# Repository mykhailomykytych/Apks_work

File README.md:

# Лабораторна робота №1 — AI-агент для автоматизації розробки та CI/CD

| | |
|---|---|
| **Студент** | Микитич Михайло Васильович |
| **Група** | КІ-407 |
| **Варіант** | 6 (номер у списку 12): TypeScript · npm scripts · Vitest |

## Опис
Репозиторій містить AI-агента **build-engineer** для GitHub Copilot (VS Code),
який генерує, складає, тестує та налаштовує CI для кросплатформного
TypeScript-проєкту `Hello World`.

- Гілка `develop` — лише агент (manifest, skills, commands) та документація.
- Гілка `feature/lab1-hello-world` — повний результат роботи агента: вихідний код,
  тести, система складання, CI-скрипти та GitHub Actions.

## Структура агента
| Елемент | Файл |
|---|---|
| Agent manifest | `.github/agents/build-engineer.agent.md` |
| Skill `project-scaffold` | `.github/skills/project-scaffold/SKILL.md` |
| Skill `build-and-test` | `.github/skills/build-and-test/SKILL.md` |
| Skill `github-actions` | `.github/skills/github-actions/SKILL.md` |
| Commands | `.github/prompts/{git-init,create-project,create-build,create-actions,check}.prompt.md` |
| Orchestrator | `.github/prompts/init.prompt.md` |

## Запуск агента (коротко)
1. Відкрити репозиторій у VS Code з увімкненим GitHub Copilot.
2. Відкрити Copilot Chat, обрати агента **build-engineer**.
3. Ввести `/init` і дочекатися звіту `init COMPLETED`.

Детально — у [docs/usage.md](docs/usage.md). Архітектура — у
[docs/architecture.md](docs/architecture.md). Журнал роботи з AI —
[docs/ai-log.md](docs/ai-log.md).

## Запуск зібраного проєкту
```bash
npm ci
npm run build
npm start              # Hello, World!
npm test               # Vitest, включно з BasicAddition
npm run package        # створює виконуваний файл bin/hello (bin\hello.exe)
./bin/hello            # Hello, World!
```
Повний CI-сценарій локально: `./scripts/ci.sh` (Linux/macOS) або `scripts\ci.bat` (Windows).

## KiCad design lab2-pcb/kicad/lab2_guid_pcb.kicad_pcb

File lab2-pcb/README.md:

# Лабораторна робота №2 — друкована плата за GUID (KiCad)

| | |
|---|---|
| **Студент** | Микитич Михайло Васильович |
| **Група** | КІ-407 |
| **САПР** | KiCad 7 (файли відкриваються в KiCad 7/8/9) |

## 1. GUID
GUID отримано хешуванням повного імені (UUID v5, SHA-1, простір імен DNS):

```python
import uuid
uuid.uuid5(uuid.NAMESPACE_DNS, "Микитич Михайло Васильович")
# 8c0f2d7a-9934-50b1-a59d-aba02fab321b
```

## 2. Розміри елементів
| Елемент | Група GUID | Символів | Розмір, мм | Пінів |
|---|---|---|---|---|
| U1 | `8c0f2d7a` | 8 | 8 × 8 | 8 |
| U2 | `9934` | 4 | 4 × 4 | 4 |
| U3 | `50b1` | 4 | 4 × 4 | 4 |
| U4 | `a59d` | 4 | 4 × 4 | 4 |
| U5 | `aba02fab321b` | 12 | 12 × 12 | 12 |

Нумерація пінів: проти годинникової стрілки від лівого верхнього (як у QFP);
пін *k* відповідає *k*-му символу групи.

## 3. Таблиця з'єднань
Однакові символи — це рівнозначні піни, тому їх з'єднано.

| Символ | Ланцюг | Піни |
|---|---|---|
| `0` | N_0 | U1.3, U3.2, U5.4 |
| `1` | N_1 | U3.4, U5.11 |
| `2` | N_2 | U1.5, U5.5, U5.10 |
| `3` | N_3 | U2.3, U5.9 |
| `5` | N_5 | U3.1, U4.2 |
| `9` | N_9 | U2.1, U2.2, U4.3 |
| `a` | N_A | U1.8, U4.1, U5.1, U5.3, U5.7 |
| `b` | N_B | U3.3, U5.2, U5.8, U5.12 |
| `d` | N_D | U1.6, U4.4 |
| `f` | N_F | U1.4, U5.6 |

Вільні піни (символ трапляється один раз) виведено на роз'єм **J1** на
лівій (меншій) стороні плати:

| Символ | Пін | J1 |
|---|---|---|
| `4` | U2.4 | J1.1 |
| `7` | U1.7 | J1.2 |
| `8` | U1.1 | J1.3 |
| `c` | U1.2 | J1.4 |

## 4. Плата
- Контур: **85.6 × 53.98 мм** (кредитна картка ID-1), радіус кутів 3.18 мм.
- 2 шари (F.Cu / B.Cu), доріжки 0.3 мм, зазор 0.25 мм, перехідні отвори 0.8/0.4 мм.
- Розміщення: U5 (найбільше зв'язків) у центрі, U1 (4 спільні ланцюги з U5) поруч,
  J1 біля U1 (3 з 4 вільних пінів належать U1).
- Трасування: кути 45°/90°, гострих кутів немає. Загальна довжина ≈ 414 мм, 4 перехідні отвори.
- **DRC: 0 порушень, 0 непід'єднаних пад** — `out/drc_report.txt`.

## 5. Файли
| Шлях | Вміст |
|---|---|
| `kicad/lab2_guid_pcb.kicad_pro` | Проєкт KiCad (відкривати цей файл) |
| `kicad/lab2_guid_pcb.kicad_sch` | Принципова схема |
| `kicad/lab2_guid_pcb.kicad_pcb` | Топологія плати |
| `kicad/guid_parts.kicad_sym`, `kicad/guid_parts.pretty/` | Власні бібліотеки символів і футпринтів U1–U5, J1 |
| `gerber/` | Gerber RS-274X + Excellon drill (готово до виробництва) |
| `out/lab2_guid_pcb_gerber.zip` | Ті самі Gerber-файли одним архівом |
| `out/schematic.pdf`, `out/pcb_layout.pdf`, `out/*.png` | Зображення схеми та плати |
| `out/drc_report.txt` | Звіт DRC |
| `tools/` | Скрипти: GUID → бібліотеки → схема → плата → трасування → DRC |

## 6. Відтворення
```bash
./build.sh
```
Скрипт заново генерує бібліотеки, схему, плату, трасування, DRC і Gerber-файли.
Скріншоти для звіту робляться в KiCad (Schematic Editor, PCB Editor, Inspect → Design Rules Checker).

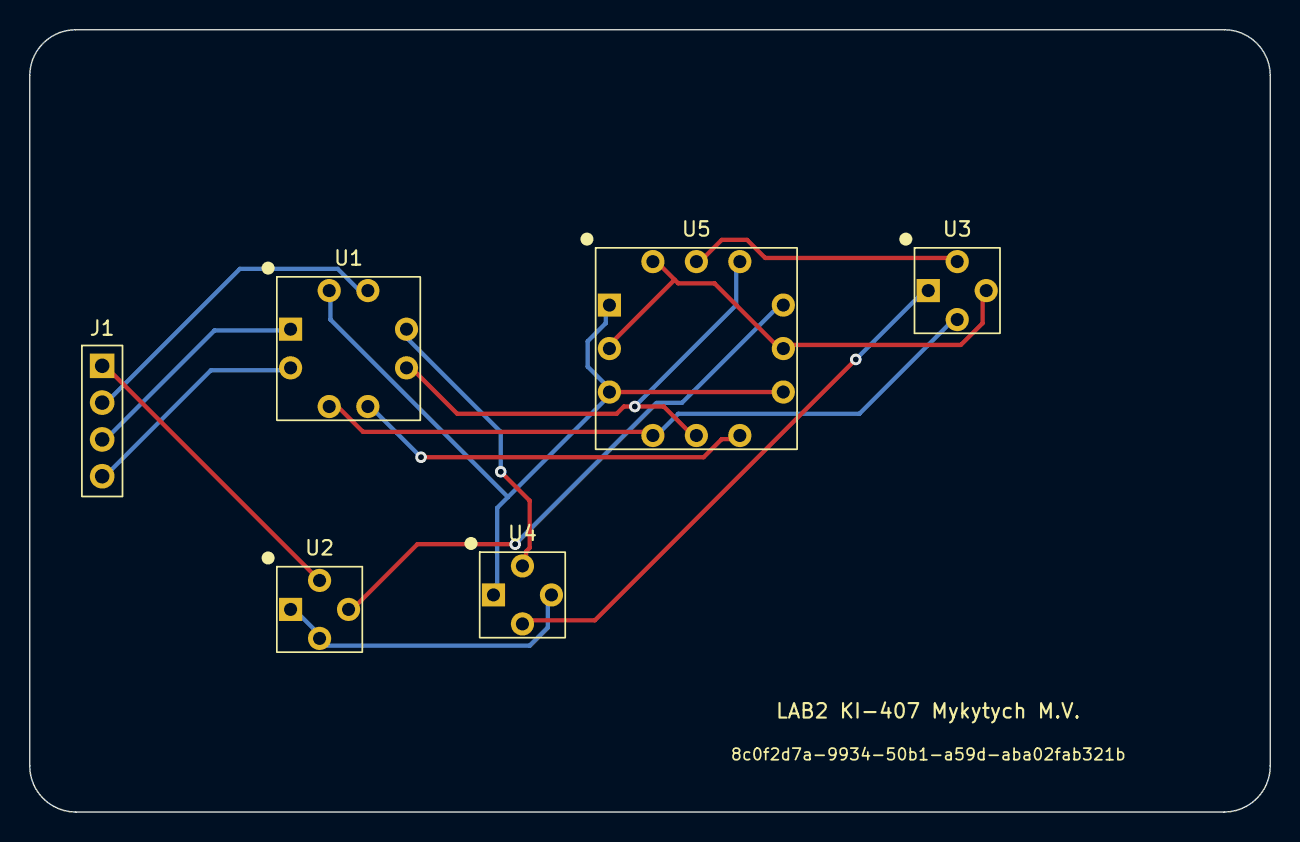
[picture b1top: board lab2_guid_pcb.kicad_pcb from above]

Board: 2 copper layers, 85.6 x 54.0 mm, 6 parts (0 on the bottom side), 14 nets.

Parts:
J1: GUID_J1_1x04_P2.54mm
U1: GUID_U1_8x8mm
U2: GUID_U2_4x4mm
U3: GUID_U3_4x4mm
U4: GUID_U4_4x4mm
U5: GUID_U5_12x12mm

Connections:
FREE_4: J1.1, U2.4
FREE_7: J1.2, U1.7
FREE_8: J1.3, U1.1
FREE_C: J1.4, U1.2
N_0: U1.3, U3.2, U5.4
N_1: U3.4, U5.11
N_2: U1.5, U5.5, U5.10
N_3: U2.3, U5.9
N_5: U3.1, U4.2
N_9: U2.1, U2.2, U4.3
N_A: U1.8, U4.1, U5.1, U5.3, U5.7
N_B: U3.3, U5.2, U5.8, U5.12
N_D: U1.6, U4.4
N_F: U1.4, U5.6
